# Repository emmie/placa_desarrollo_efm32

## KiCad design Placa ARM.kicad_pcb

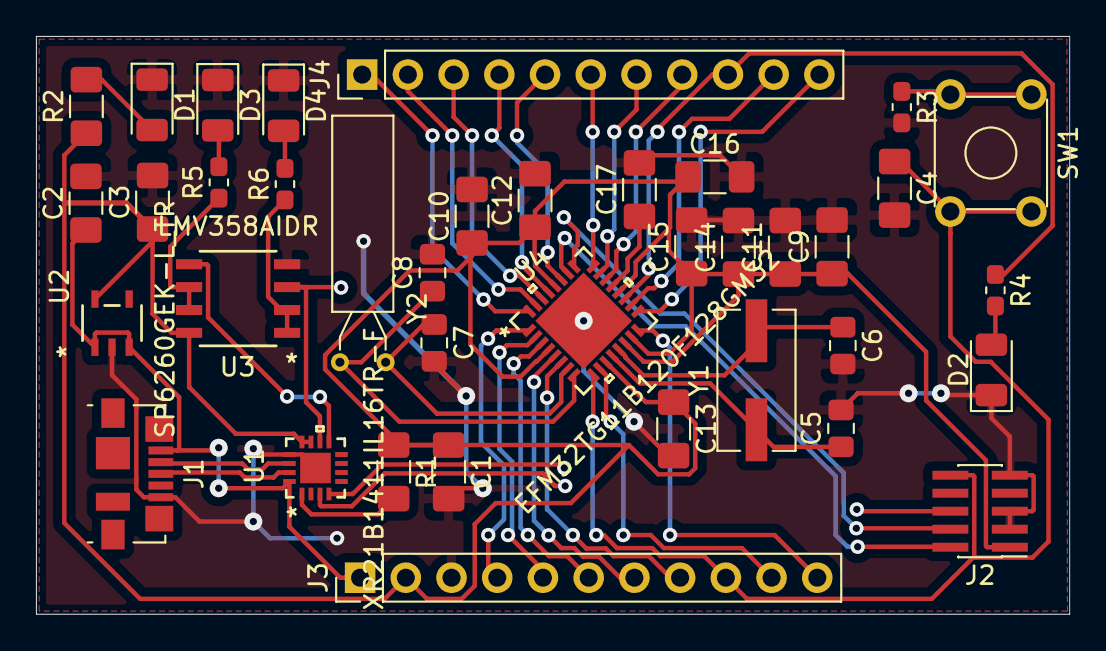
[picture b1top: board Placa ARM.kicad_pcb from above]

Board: 2 copper layers, 57.4 x 32.1 mm, 38 parts (0 on the bottom side), 39 nets.

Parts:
C1, C4, C10, C12, C14, C16: 100n; C_1206_3216Metric_Pad1.42x1.75mm_HandSolder
C2, C3, C17: 1u; C_1206_3216Metric_Pad1.42x1.75mm_HandSolder
C5, C6: 12p; C_0805_2012Metric_Pad1.15x1.40mm_HandSolder
C7, C8: 22p; C_0805_2012Metric_Pad1.15x1.40mm_HandSolder
C9, C11: 10u; C_1206_3216Metric_Pad1.42x1.75mm_HandSolder
C13, C15: 10n; C_1206_3216Metric_Pad1.42x1.75mm_HandSolder
D1: PWR; LED_1206_3216Metric
D2: USR; LED_1206_3216Metric
D3: TX; LED_1206_3216Metric
D4: RX; LED_1206_3216Metric
J1: USB_B_Micro; USB_Micro-B_Molex_47346-0001
J2: Conn_ARM_JTAG_SWD_10; PinHeader_2x05_P1.00mm_Vertical_SMD
J3, J4: Conn_01x11; PinHeader_1x11_P2.54mm_Vertical
R1: 10k; R_1206_3216Metric_Pad1.42x1.75mm_HandSolder
R2: 1k; R_1206_3216Metric_Pad1.42x1.75mm_HandSolder
R3: 100R; R_0603_1608Metric_Pad1.05x0.95mm_HandSolder
R4, R5, R6: 1k; R_0603_1608Metric_Pad1.05x0.95mm_HandSolder
SW1: SW_Push_Dual; SW_TH_Tactile_Omron_B3F-10xx
U1: XR21B1411IL16TR-F
U2: SP6260GEK-L_TR; SP6260GEKLTR
U3: LMV358AIDR
U4: EFM32TG11B120F128GM32
Y1: 32MHz; Crystal_SMD_ECS_CSM3X-2Pin_7.6x4.1mm
Y2: 32.768KHz; Crystal_AT310_D3.0mm_L10.0mm_Horizontal

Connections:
+3V3: C1.1, C3.1, C9.1, C10.1, C11.1, C12.1, C13.1, C14.1, C15.1, C16.1, J2.1, J3.2, R1.1, R2.1, U1.11, U1.12, U2.5, U3.8, U4.4, U4.11, U4.14, U4.15, U4.20, U4.28
+5V: C2.1, J1.1, J3.1, U1.16, U2.1, U2.3
/Fuente de Poder/USB_D+: J1.3, U1.15
/Fuente de Poder/USB_D-: J1.2, U1.14
/IU5: C4.1, J2.10, J3.9, SW1.2, SW1.4, U4.9
/IU6: J2.2, U1.10, U3.3, U4.26
/IU7: J2.6, J4.5, U1.9, U3.5, U4.27
/IU8: J4.11, U1.4, U4.17
/IU9: J4.10, U1.3, U4.18
/Interfaz de Usuario/MCU_PA0: J3.4, U4.1
/Interfaz de Usuario/MCU_PA1: J3.5, U4.2
/Interfaz de Usuario/MCU_PA2: J3.6, U4.3
/Interfaz de Usuario/MCU_PB11: J3.10, U4.10
/Interfaz de Usuario/MCU_PC0: J3.7, U4.5
/Interfaz de Usuario/MCU_PC1: J3.8, U4.6
/Interfaz de Usuario/MCU_PC13: J4.8, U4.22
/Interfaz de Usuario/MCU_PC14: J4.7, U4.23
/Interfaz de Usuario/MCU_PC15: J4.6, U4.24
/Interfaz de Usuario/MCU_PD4: J3.11, U4.16
/Interfaz de Usuario/MCU_PD7: J4.9, R4.1, U4.19
/Interfaz de Usuario/MCU_PE10: J4.4, U4.29
/Interfaz de Usuario/MCU_PE11: J4.3, U4.30
/Interfaz de Usuario/MCU_PE12: J4.2, U4.31
/Interfaz de Usuario/MCU_PE13: J4.1, U4.32
/Interfaz de Usuario/MCU_PF0: J2.4, U4.25
/Microcontrolador/MCU_PB7: C7.1, U4.7, Y2.1
/Microcontrolador/MCU_PB8: C8.1, U4.8, Y2.2
/Microcontrolador/MCU_PB13: C5.1, U4.12, Y1.1
/Microcontrolador/MCU_PB14: C6.1, U4.13, Y1.2
GND: C1.2, C2.2, C3.2, C4.2, C5.2, C6.2, C7.2, C8.2, C9.2, C10.2, C11.2, C12.2, C13.2, C14.2, C15.2, C16.2, C17.2, D1.1, D2.1, D3.1, D4.1, J1.5, J2.3, J2.5, J2.9, J3.3, R3.2, U1.13, U1.17, U2.2, U3.4, U4.33
unnamed: C17.1, U4.21
unnamed: D1.2, R2.2
unnamed: D2.2, R4.2
unnamed: D3.2, R5.2
unnamed: D4.2, R6.2
unnamed: R1.2, U1.1
unnamed: R3.1, SW1.1, SW1.3
unnamed: R5.1, U3.6, U3.7
unnamed: R6.1, U3.1, U3.2

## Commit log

2020-09-04 Issue #1: Conexion inicial de componetes
2020-09-05 Issue #1: Correción de las conexiones Bus
2020-09-11 Issue #1: Cambio de regulador de voltaje
    Se reemplazó el MAX8887 de Maxim por el SP6260 de Maxlinear.
2020-09-12 Issue #1: Cambio de conector USB-UART
    Se agrega un conector para todos los pines UART ofrecidos por el IC
    XR21B1411 de Maxlinear.
2020-09-15 Issue #1: Mejora de la funcionalidad de reset
2020-09-15 Issue #1: Cambio de conector GPIOs
2020-09-15 Issue #1: Incorporación de conector para debug
    Se agrega el conector estandar para ARM de 10 pines para debug con SWD.
    Como referencia use la nota de aplicación AN0002.1
2020-09-15 Issue #1: Se agregan LEDs para líneas TX/RX de UART
    Se agregan los LEDs para indicar comunicación vía UART. Se utilizó un
    OpAmp para evitar un consumo excesivo de corriente en las líneas de
    comunicación.
    Referencia: https://bit.ly/2E7PuVE
2020-09-16 Issue #2: Primer acercamiento al diseño de la PCB
    Se modificaron los conectores externos de los pines GPIOs (para no
    exponer los que se conectan a los cristales) y se realizó la
    distribución inicial de componentes en la placa (sin conectarlos)
2020-09-28 Issue #2: PCB lista para primera prueba de concepto

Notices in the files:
parts and their libraries:
Copyright 2016 Accelerated Designs. All rights reserved.
